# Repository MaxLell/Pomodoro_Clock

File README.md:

# Pomodoro_Clock

## Why?
This device forces me to take breaks in regular intervals throughout the day. Research has shown that the brain grows tired when being forced to focus on tasks on a prolonged time. (I think everybody can also observe this in his own life). But research also shows, that if you take regular breaks, you do not deplete your mental ressources as quickly and you can focus for longer hours.

So this is basically what this device (will) is about. It will sit on my desk and ping me, when I need to take a break, and not only ping me, but rather shine a bright light at me, so that I actually get my lazy a** up and move around for a couple of minutes - day in day out. 
You might say: Well you can also set a timer on your smartphone and go from there, to which I reply: Yeah you can, but if you want to do that day-in, day-out, you need a lot of will power and the most perfect habits the world has ever witnessed in man-kind. I am not such a person. 

And for this reason I built this device.

## What?
So what is this marvelous device I am talking about? Well I am glad you are asking: It is basically a box of lights, where you can set up the interval for which you want to work (the next cycle is composed of Worktime and Breaktime). Then it will run a countdown timer.

## How?
- This project is partially also a way for myself to learn and work on a complicated challenge: I already resolved the architecture of this multi-module Architecture (using a Message Broker, so that these modules only exchange data via this Messages-Interface - Observer Pattern). Or working on the implementation of high-speed low level peripherals, which require the usage of the DMA.

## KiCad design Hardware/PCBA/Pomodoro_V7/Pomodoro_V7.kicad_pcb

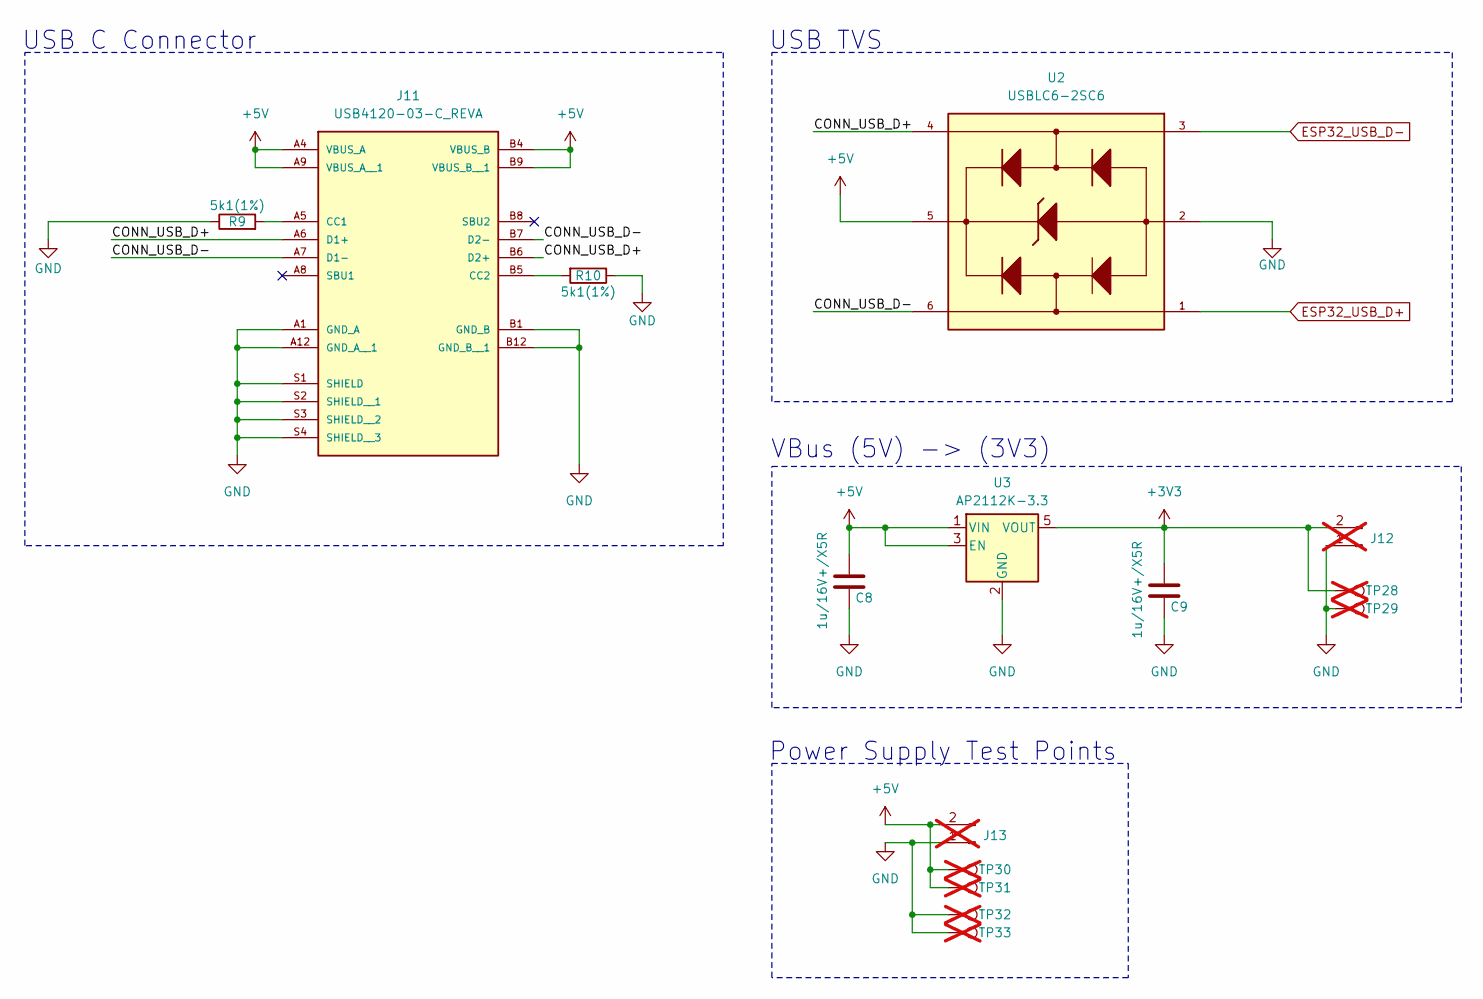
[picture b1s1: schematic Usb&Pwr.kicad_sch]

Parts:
C8, C9: 1u/16V+/X5R; C_0805_2012Metric
J11: USB4120-03-C_REVA; GCT_USB4120-03-C_REVA; PARTREV A
J12, J13: Conn_01x02_Pin; PinHeader_1x02_P2.54mm_Vertical; not fitted
R9, R10: 5k1(1%); R_0805_2012Metric; Part ID CR0805-FX-5101ELF
TP28, TP29, TP30, TP31, TP32, TP33: TestPoint; TestPoint_Pad_D1.0mm; not fitted
U2: USBLC6-2SC6; SOT95P280X145-6N; Mfg Part # USBLC6-2SC6
U3: AP2112K-3.3; SOT-23-5; Mfg Part # AP2112K-3.3TRG1

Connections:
+3V3: C9.1, J12.2, TP28.1, U3.5 (VOUT); also elsewhere on the board
+5V: C8.1, J11.A4 (VBUS_A), J11.A9 (VBUS_A__1), J11.B4 (VBUS_B), J11.B9 (VBUS_B__1), J13.2, TP30.1, TP31.1, U2.5, U3.1 (VIN), U3.3 (EN); also elsewhere on the board
/USB Conn and PWR /CONN_USB_D+: J11.A6 (D1+), J11.B6 (D2+), U2.4
/USB Conn and PWR /CONN_USB_D-: J11.A7 (D1-), J11.B7 (D2-), U2.6
ESP32_USB_D+: U2.1; also elsewhere on the board
ESP32_USB_D-: U2.3; also elsewhere on the board
GND: C8.2, C9.2, J11.A1 (GND_A), J11.A12 (GND_A__1), J11.B1 (GND_B), J11.B12 (GND_B__1), J11.S1 (SHIELD), J11.S2 (SHIELD__1), J11.S3 (SHIELD__2), J11.S4 (SHIELD__3), J12.1, J13.1, R9.1, R10.1, TP29.1, TP32.1, TP33.1, U2.2, U3.2 (GND); also elsewhere on the board
unnamed: J11.A5 (CC1), R9.2
unnamed: J11.B5 (CC2), R10.2

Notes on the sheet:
USB TVS
Power Supply Test Points
VBus (5V) -> (3V3)
USB C Connector

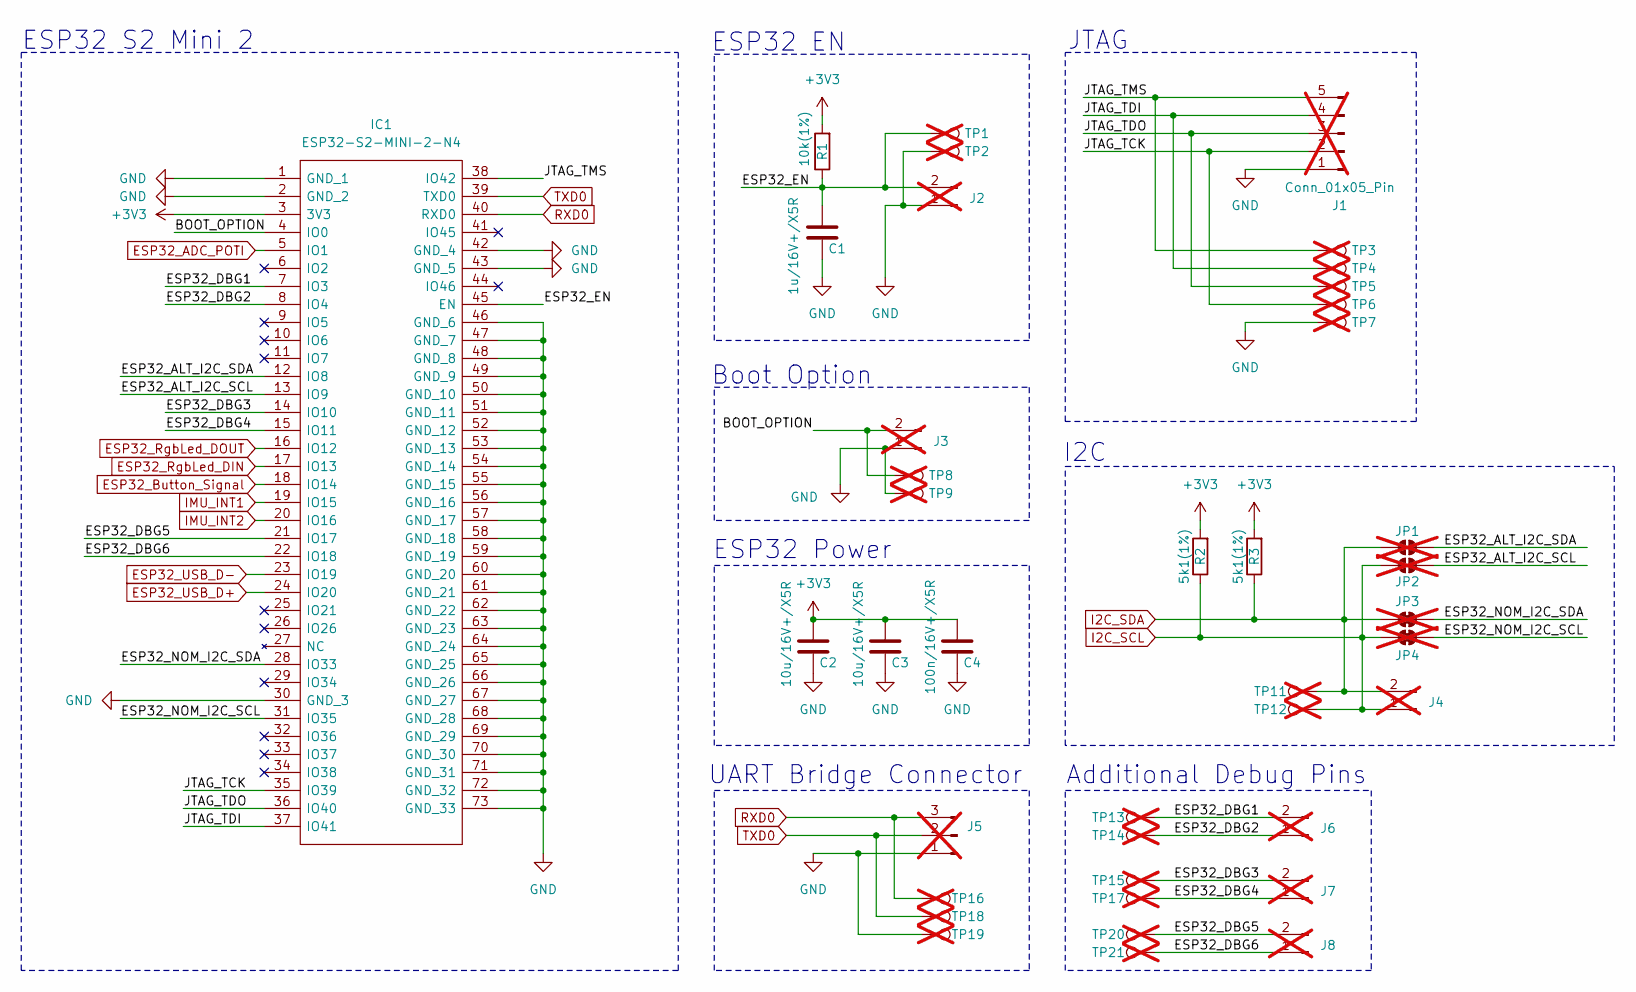
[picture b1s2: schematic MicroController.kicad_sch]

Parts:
C1: 1u/16V+/X5R; C_0805_2012Metric
C2, C3: 10u/16V+/X5R; C_0805_2012Metric
C4: 100n/16V+/X5R; C_0805_2012Metric
IC1: ESP32-S2-MINI-2-N4; ESP32-S2-MINI-1; Mouser Part Number 356-ESP32MINI-2-N4
J1: Conn_01x05_Pin; PinHeader_1x05_P2.54mm_Vertical; not fitted
J2, J3, J4, J6, J7, J8: Conn_01x02_Pin; PinHeader_1x02_P2.54mm_Vertical; not fitted
J5: Conn_01x03_Pin; PinHeader_1x03_P2.54mm_Vertical; not fitted
JP1, JP2: SolderJumper_2_Open; SolderJumper-2_P1.3mm_Open_RoundedPad1.0x1.5mm; not fitted
JP3, JP4: SolderJumper_2_Bridged; SolderJumper-2_P1.3mm_Bridged2Bar_RoundedPad1.0x1.5mm; not fitted
R1: 10k(1%); R_0805_2012Metric; Part ID CR0805-FX-5101ELF
R2, R3: 5k1(1%); R_0805_2012Metric; Part ID CR0805-FX-5101ELF
TP1, TP2, TP3, TP4, TP5, TP6, TP7, TP8, TP9, TP11, TP12, TP13, TP14, TP15, TP16, TP17, TP18, TP19, TP20, TP21: TestPoint; TestPoint_Pad_D1.0mm; not fitted

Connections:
+3V3: C2.1, C3.1, C4.1, IC1.3 (3V3), R1.2, R2.2, R3.2; also elsewhere on the board
/MicroController/BOOT_OPTION: IC1.4 (IO0), J3.2, TP8.1
/MicroController/ESP32_ALT_I2C_SCL: IC1.13 (IO9), JP2.1 (A)
/MicroController/ESP32_ALT_I2C_SDA: IC1.12 (IO8), JP1.2 (B)
/MicroController/ESP32_DBG1: IC1.7 (IO3), J6.2, TP13.1
/MicroController/ESP32_DBG2: IC1.8 (IO4), J6.1, TP14.1
/MicroController/ESP32_DBG3: IC1.14 (IO10), J7.2, TP15.1
/MicroController/ESP32_DBG4: IC1.15 (IO11), J7.1, TP17.1
/MicroController/ESP32_DBG5: IC1.21 (IO17), J8.2, TP20.1
/MicroController/ESP32_DBG6: IC1.22 (IO18), J8.1, TP21.1
/MicroController/ESP32_EN: C1.1, IC1.45 (EN), J2.2, R1.1, TP1.1
/MicroController/ESP32_NOM_I2C_SCL: IC1.31 (IO35), JP4.1 (A)
/MicroController/ESP32_NOM_I2C_SDA: IC1.28 (IO33), JP3.2 (B)
/MicroController/JTAG_TCK: IC1.35 (IO39), J1.2, TP6.1
/MicroController/JTAG_TDI: IC1.37 (IO41), J1.4, TP4.1
/MicroController/JTAG_TDO: IC1.36 (IO40), J1.3, TP5.1
/MicroController/JTAG_TMS: IC1.38 (IO42), J1.5, TP3.1
ESP32_ADC_POTI: IC1.5 (IO1); also elsewhere on the board
ESP32_Button_Signal: IC1.18 (IO14); also elsewhere on the board
ESP32_RgbLed_DIN: IC1.17 (IO13); also elsewhere on the board
ESP32_RgbLed_DOUT: IC1.16 (IO12); also elsewhere on the board
ESP32_USB_D+: IC1.24 (IO20); also elsewhere on the board
ESP32_USB_D-: IC1.23 (IO19); also elsewhere on the board
GND: C1.2, C2.2, C3.2, C4.2, IC1.1 (GND_1), IC1.2 (GND_2), IC1.30 (GND_3), IC1.42 (GND_4), IC1.43 (GND_5), IC1.46 (GND_6), IC1.47 (GND_7), IC1.48 (GND_8), IC1.49 (GND_9), IC1.50 (GND_10), IC1.51 (GND_11), IC1.52 (GND_12), IC1.53 (GND_13), IC1.54 (GND_14), IC1.55 (GND_15), IC1.56 (GND_16), IC1.57 (GND_17), IC1.58 (GND_18), IC1.59 (GND_19), IC1.60 (GND_20), IC1.61 (GND_21), IC1.62 (GND_22), IC1.63 (GND_23), IC1.64 (GND_24), IC1.65 (GND_25), IC1.66 (GND_26), IC1.67 (GND_27), IC1.68 (GND_28), IC1.69 (GND_29), IC1.70 (GND_30), IC1.71 (GND_31), IC1.72 (GND_32), IC1.73 (GND_33), J1.1, J2.1, J3.1, J5.1, TP2.1, TP7.1, TP9.1, TP19.1; also elsewhere on the board
I2C_SCL: J4.1, JP2.2 (B), JP4.2 (B), R2.1, TP12.1; also elsewhere on the board
I2C_SDA: J4.2, JP1.1 (A), JP3.1 (A), R3.1, TP11.1; also elsewhere on the board
IMU_INT1: IC1.19 (IO15); also elsewhere on the board
IMU_INT2: IC1.20 (IO16); also elsewhere on the board
RXD0: IC1.40 (RXD0), J5.3, TP16.1
TXD0: IC1.39 (TXD0), J5.2, TP18.1

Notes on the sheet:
ESP32 Power
ESP32 EN
Additional Debug Pins
ESP32 S2 Mini 2
UART Bridge Connector
JTAG
I2C
Boot Option

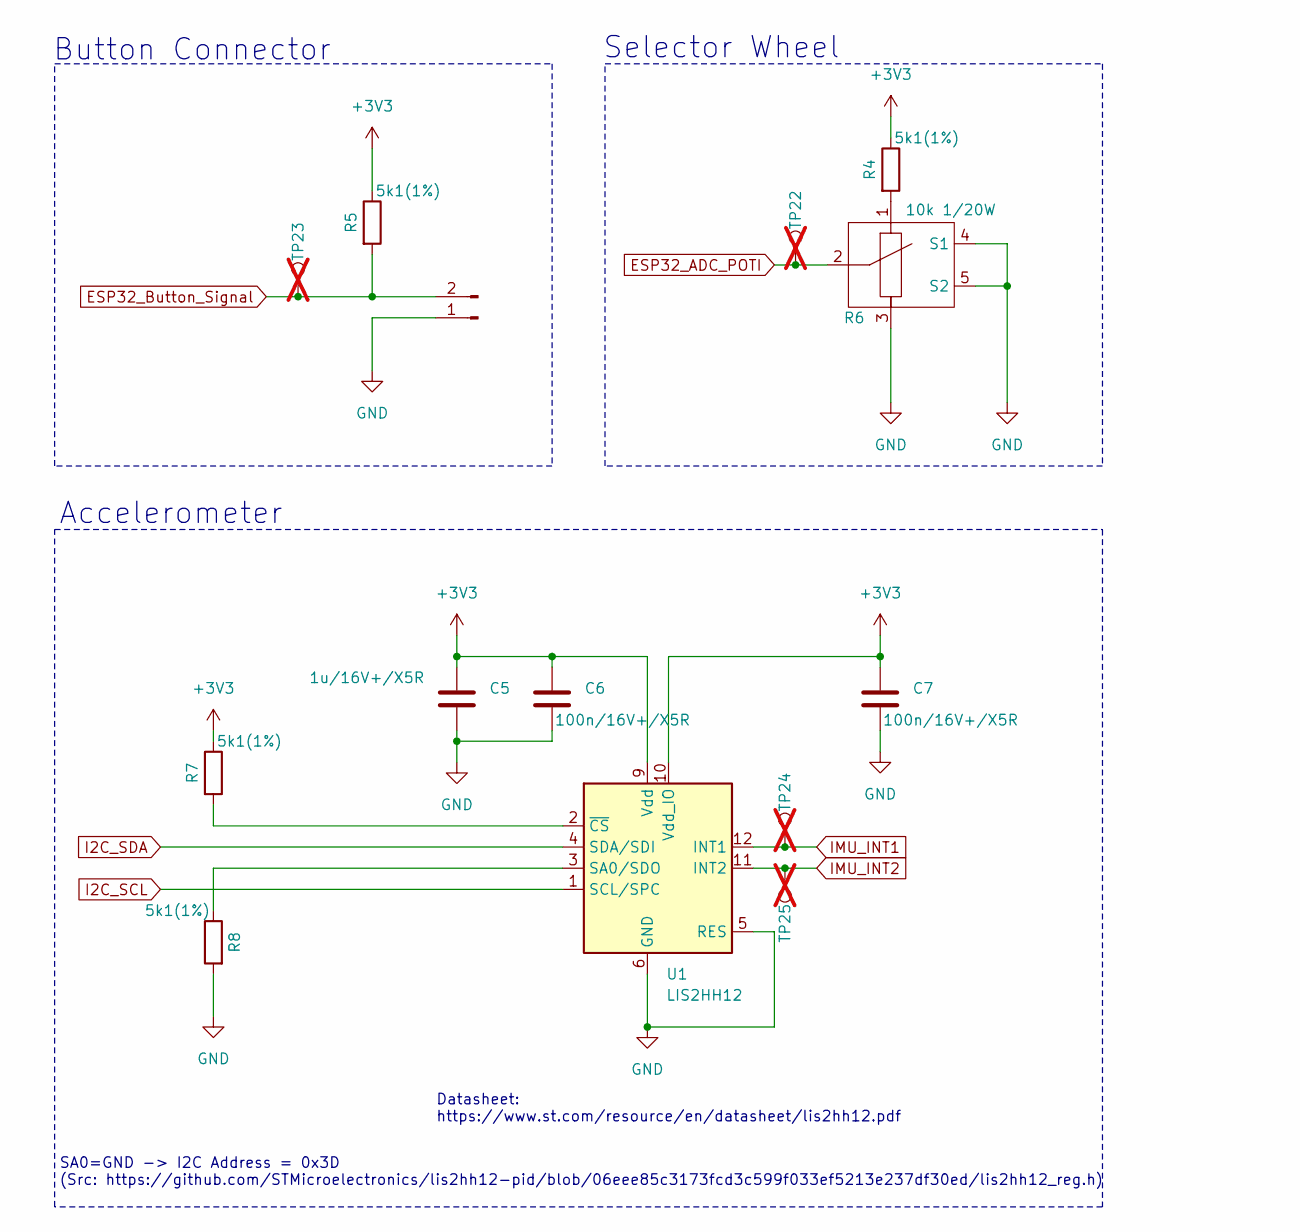
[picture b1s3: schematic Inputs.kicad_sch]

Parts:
C5: 1u/16V+/X5R; C_0805_2012Metric; MPN 0805B105K250DC
C6, C7: 100n/16V+/X5R; C_0805_2012Metric; MPN CC0805KRX7R9BB104
J10: Conn_01x02_Pin; PinHeader_1x02_P2.54mm_Horizontal
R4, R5, R7, R8: 5k1(1%); R_0805_2012Metric; Part ID CR0805-FX-5101ELF
R6: 10k 1/20W; Pot; Mfg Part # PTV09A-4025F-B103
TP22, TP23, TP24, TP25: TestPoint; TestPoint_Pad_D1.0mm; not fitted
U1: LIS2HH12; Kionix_LGA-12_2x2mm_P0.5mm_LayoutBorder2x4y; MPN LIS2HH12

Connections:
+3V3: C5.2, C6.2, C7.2, R4.1, R5.1, R7.1, U1.9 (Vdd), U1.10 (Vdd_IO); also elsewhere on the board
ESP32_ADC_POTI: R6.2, TP22.1; also elsewhere on the board
ESP32_Button_Signal: J10.2, R5.2, TP23.1; also elsewhere on the board
GND: C5.1, C6.1, C7.1, J10.1, R6.3, R6.4 (S1), R6.5 (S2), R8.2, U1.5 (RES), U1.6 (GND), U1.7 (GND), U1.8 (GND); also elsewhere on the board
I2C_SCL: U1.1 (SCL/SPC); also elsewhere on the board
I2C_SDA: U1.4 (SDA/SDI); also elsewhere on the board
IMU_INT1: TP24.1, U1.12 (INT1); also elsewhere on the board
IMU_INT2: TP25.1, U1.11 (INT2); also elsewhere on the board
unnamed: R4.2, R6.1
unnamed: R8.1, U1.3 (SA0/SDO)
unnamed: R7.2, U1.2 (~CS)

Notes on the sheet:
Accelerometer
SA0=GND -> I2C Address = 0x3D (Src: https://github.com/STMicroelectronics/lis2hh12-pid/blob/06eee85c3173fcd3c599f033ef5213e237df30ed/lis2hh12_reg.h)
Button Connector
Datasheet: https://www.st.com/resource/en/datasheet/lis2hh12.pdf
Selector Wheel

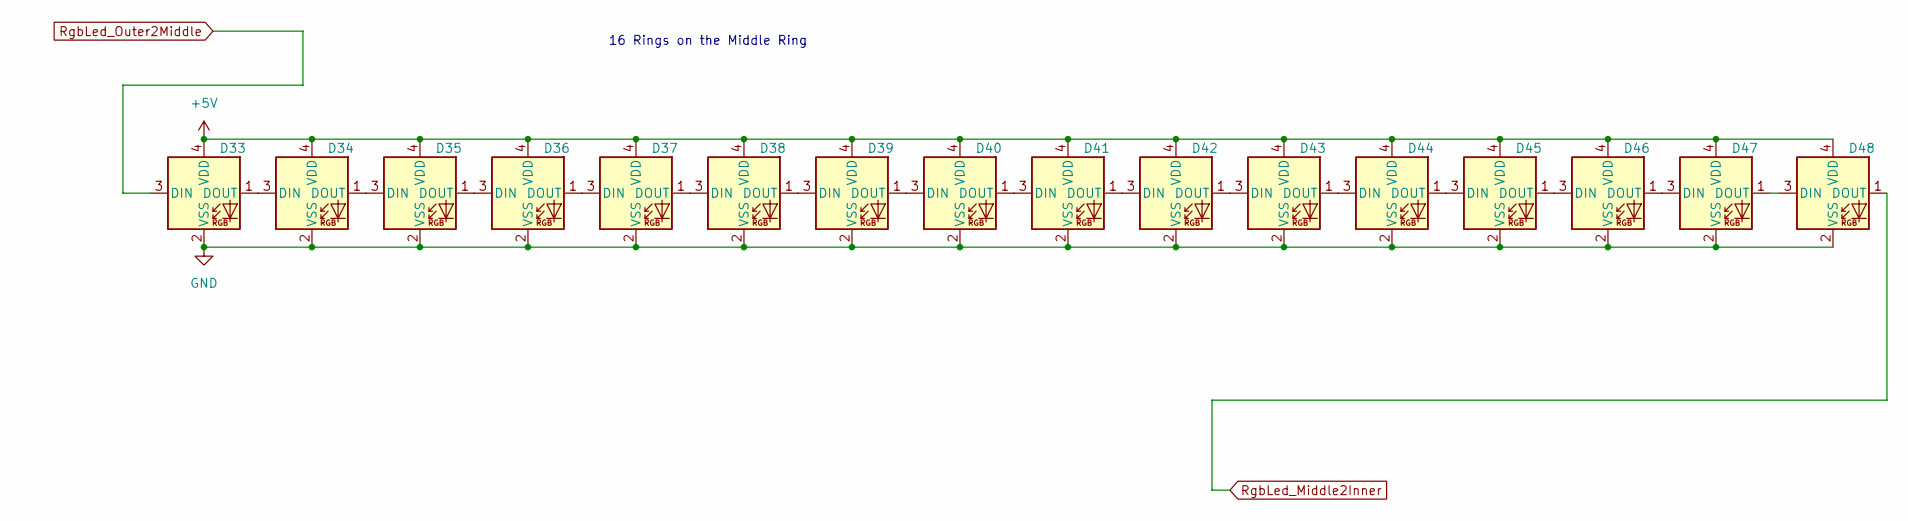
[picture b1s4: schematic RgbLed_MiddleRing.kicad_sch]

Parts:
D33, D34, D35, D36, D37, D38, D39, D40, D41, D42, D43, D44, D45, D46, D47, D48: WS2812B-2020; LED_WS2812B-2020_PLCC4_2.0x2.0mm; MPN WS2812B-2020

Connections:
+5V: D33.4 (VDD), D34.4 (VDD), D35.4 (VDD), D36.4 (VDD), D37.4 (VDD), D38.4 (VDD), D39.4 (VDD), D40.4 (VDD), D41.4 (VDD), D42.4 (VDD), D43.4 (VDD), D44.4 (VDD), D45.4 (VDD), D46.4 (VDD), D47.4 (VDD), D48.4 (VDD); also elsewhere on the board
GND: D33.2 (VSS), D34.2 (VSS), D35.2 (VSS), D36.2 (VSS), D37.2 (VSS), D38.2 (VSS), D39.2 (VSS), D40.2 (VSS), D41.2 (VSS), D42.2 (VSS), D43.2 (VSS), D44.2 (VSS), D45.2 (VSS), D46.2 (VSS), D47.2 (VSS), D48.2 (VSS); also elsewhere on the board
unnamed: D33.1 (DOUT), D34.3 (DIN)
unnamed: D34.1 (DOUT), D35.3 (DIN)
unnamed: D35.1 (DOUT), D36.3 (DIN)
unnamed: D36.1 (DOUT), D37.3 (DIN)
unnamed: D37.1 (DOUT), D38.3 (DIN)
unnamed: D38.1 (DOUT), D39.3 (DIN)
unnamed: D39.1 (DOUT), D40.3 (DIN)
unnamed: D40.1 (DOUT), D41.3 (DIN)
unnamed: D41.1 (DOUT), D42.3 (DIN)
unnamed: D42.1 (DOUT), D43.3 (DIN)
unnamed: D43.1 (DOUT), D44.3 (DIN)
unnamed: D44.1 (DOUT), D45.3 (DIN)
unnamed: D45.1 (DOUT), D46.3 (DIN)
unnamed: D46.1 (DOUT), D47.3 (DIN)
unnamed: D47.1 (DOUT), D48.3 (DIN)
RgbLed_Middle2Inner: D48.1 (DOUT); also elsewhere on the board
RgbLed_Outer2Middle: D33.3 (DIN); also elsewhere on the board

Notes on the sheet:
16 Rings on the Middle Ring

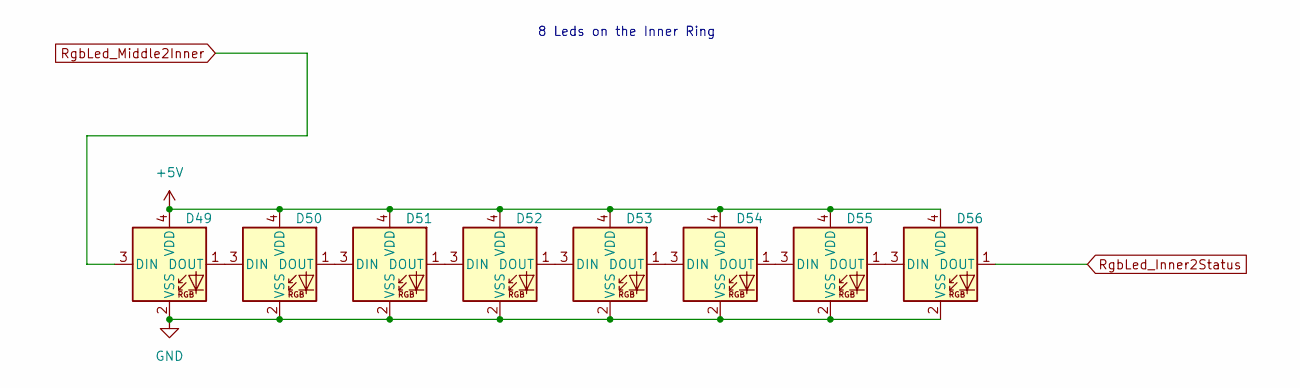
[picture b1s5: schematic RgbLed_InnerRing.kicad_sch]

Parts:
D49, D50, D51, D52, D53, D54, D55, D56: WS2812B-2020; LED_WS2812B-2020_PLCC4_2.0x2.0mm; MPN WS2812B-2020

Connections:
+5V: D49.4 (VDD), D50.4 (VDD), D51.4 (VDD), D52.4 (VDD), D53.4 (VDD), D54.4 (VDD), D55.4 (VDD), D56.4 (VDD); also elsewhere on the board
GND: D49.2 (VSS), D50.2 (VSS), D51.2 (VSS), D52.2 (VSS), D53.2 (VSS), D54.2 (VSS), D55.2 (VSS), D56.2 (VSS); also elsewhere on the board
unnamed: D49.1 (DOUT), D50.3 (DIN)
unnamed: D50.1 (DOUT), D51.3 (DIN)
unnamed: D51.1 (DOUT), D52.3 (DIN)
unnamed: D52.1 (DOUT), D53.3 (DIN)
unnamed: D53.1 (DOUT), D54.3 (DIN)
unnamed: D54.1 (DOUT), D55.3 (DIN)
unnamed: D55.1 (DOUT), D56.3 (DIN)
RgbLed_Inner2Status: D56.1 (DOUT); also elsewhere on the board
RgbLed_Middle2Inner: D49.3 (DIN); also elsewhere on the board

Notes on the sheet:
8 Leds on the Inner Ring

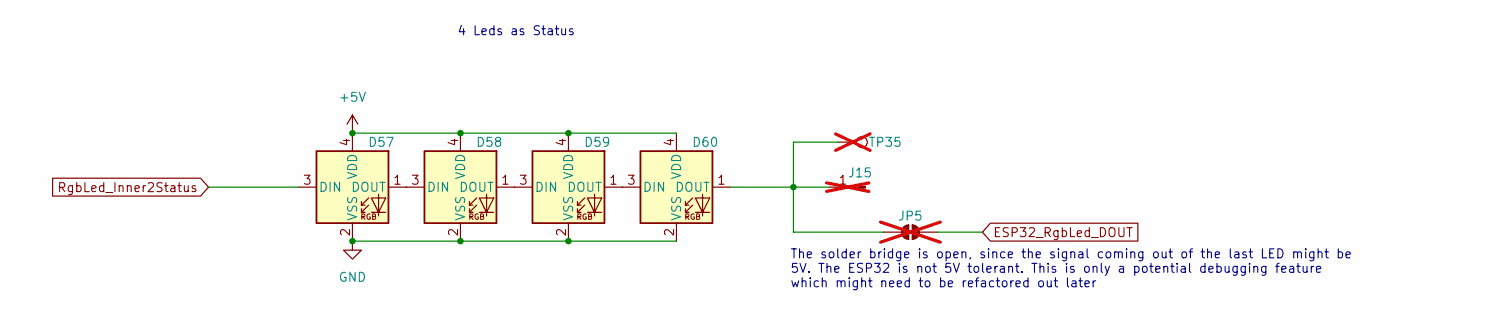
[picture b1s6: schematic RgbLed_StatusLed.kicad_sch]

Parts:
D57, D58, D59, D60: WS2812B-2020; LED_WS2812B-2020_PLCC4_2.0x2.0mm; MPN WS2812B-2020
J15: Conn_01x01_Pin; PinHeader_1x01_P2.54mm_Vertical; not fitted
JP5: SolderJumper_2_Open; SolderJumper-2_P1.3mm_Open_RoundedPad1.0x1.5mm; not fitted
TP35: TestPoint; TestPoint_Pad_D1.0mm; not fitted

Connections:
+5V: D57.4 (VDD), D58.4 (VDD), D59.4 (VDD), D60.4 (VDD); also elsewhere on the board
ESP32_RgbLed_DOUT: JP5.2 (B); also elsewhere on the board
GND: D57.2 (VSS), D58.2 (VSS), D59.2 (VSS), D60.2 (VSS); also elsewhere on the board
unnamed: D57.1 (DOUT), D58.3 (DIN)
unnamed: D58.1 (DOUT), D59.3 (DIN)
unnamed: D59.1 (DOUT), D60.3 (DIN)
unnamed: D60.1 (DOUT), J15.1, JP5.1 (A), TP35.1
RgbLed_Inner2Status: D57.3 (DIN); also elsewhere on the board

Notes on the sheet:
4 Leds as Status
The solder bridge is open, since the signal coming out of the last LED might be 5V. The ESP32 is not 5V tolerant. This is only a potential debugging feature which might need to be refactored out later

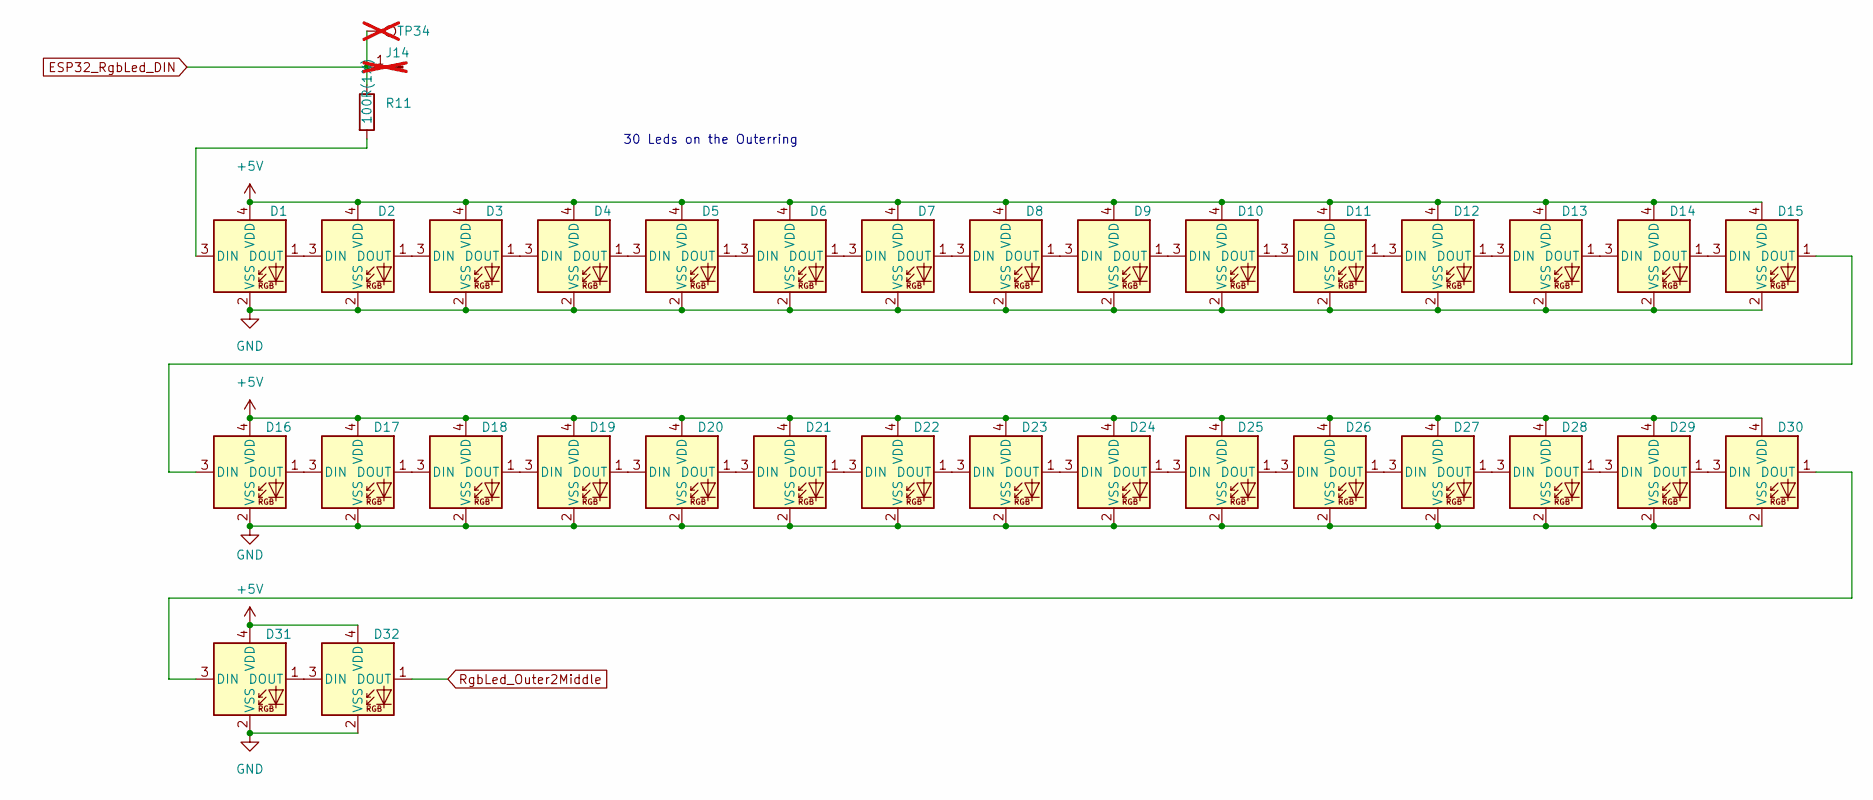
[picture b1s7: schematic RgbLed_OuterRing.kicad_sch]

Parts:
D1, D2, D3, D4, D5, D6, D7, D8, D9, D10, D11, D12, D13, D14, D15, D16, D17, D18, D19, D20, D21, D22, D23, D24, D25, D26, D27, D28, D29, D30, D31, D32: WS2812B-2020; LED_WS2812B-2020_PLCC4_2.0x2.0mm; MPN WS2812B-2020
J14: Conn_01x01_Pin; PinHeader_1x01_P2.54mm_Vertical; not fitted
R11: 100R(1%); R_0805_2012Metric; MPN RC0805FR-07100RL
TP34: TestPoint; TestPoint_Pad_D1.0mm; not fitted

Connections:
+5V: D1.4 (VDD), D2.4 (VDD), D3.4 (VDD), D4.4 (VDD), D5.4 (VDD), D6.4 (VDD), D7.4 (VDD), D8.4 (VDD), D9.4 (VDD), D10.4 (VDD), D11.4 (VDD), D12.4 (VDD), D13.4 (VDD), D14.4 (VDD), D15.4 (VDD), D16.4 (VDD), D17.4 (VDD), D18.4 (VDD), D19.4 (VDD), D20.4 (VDD), D21.4 (VDD), D22.4 (VDD), D23.4 (VDD), D24.4 (VDD), D25.4 (VDD), D26.4 (VDD), D27.4 (VDD), D28.4 (VDD), D29.4 (VDD), D30.4 (VDD), D31.4 (VDD), D32.4 (VDD); also elsewhere on the board
ESP32_RgbLed_DIN: J14.1, R11.1, TP34.1; also elsewhere on the board
GND: D1.2 (VSS), D2.2 (VSS), D3.2 (VSS), D4.2 (VSS), D5.2 (VSS), D6.2 (VSS), D7.2 (VSS), D8.2 (VSS), D9.2 (VSS), D10.2 (VSS), D11.2 (VSS), D12.2 (VSS), D13.2 (VSS), D14.2 (VSS), D15.2 (VSS), D16.2 (VSS), D17.2 (VSS), D18.2 (VSS), D19.2 (VSS), D20.2 (VSS), D21.2 (VSS), D22.2 (VSS), D23.2 (VSS), D24.2 (VSS), D25.2 (VSS), D26.2 (VSS), D27.2 (VSS), D28.2 (VSS), D29.2 (VSS), D30.2 (VSS), D31.2 (VSS), D32.2 (VSS); also elsewhere on the board
unnamed: D1.3 (DIN), R11.2
unnamed: D1.1 (DOUT), D2.3 (DIN)
unnamed: D2.1 (DOUT), D3.3 (DIN)
unnamed: D3.1 (DOUT), D4.3 (DIN)
unnamed: D4.1 (DOUT), D5.3 (DIN)
unnamed: D5.1 (DOUT), D6.3 (DIN)
unnamed: D6.1 (DOUT), D7.3 (DIN)
unnamed: D7.1 (DOUT), D8.3 (DIN)
unnamed: D8.1 (DOUT), D9.3 (DIN)
unnamed: D9.1 (DOUT), D10.3 (DIN)
unnamed: D10.1 (DOUT), D11.3 (DIN)
unnamed: D11.1 (DOUT), D12.3 (DIN)
unnamed: D12.1 (DOUT), D13.3 (DIN)
unnamed: D13.1 (DOUT), D14.3 (DIN)
unnamed: D14.1 (DOUT), D15.3 (DIN)
unnamed: D15.1 (DOUT), D16.3 (DIN)
unnamed: D16.1 (DOUT), D17.3 (DIN)
unnamed: D17.1 (DOUT), D18.3 (DIN)
unnamed: D18.1 (DOUT), D19.3 (DIN)
unnamed: D19.1 (DOUT), D20.3 (DIN)
unnamed: D20.1 (DOUT), D21.3 (DIN)
unnamed: D21.1 (DOUT), D22.3 (DIN)
unnamed: D22.1 (DOUT), D23.3 (DIN)
unnamed: D23.1 (DOUT), D24.3 (DIN)
unnamed: D24.1 (DOUT), D25.3 (DIN)
unnamed: D25.1 (DOUT), D26.3 (DIN)
unnamed: D26.1 (DOUT), D27.3 (DIN)
unnamed: D27.1 (DOUT), D28.3 (DIN)
unnamed: D28.1 (DOUT), D29.3 (DIN)
unnamed: D29.1 (DOUT), D30.3 (DIN)
unnamed: D30.1 (DOUT), D31.3 (DIN)
unnamed: D31.1 (DOUT), D32.3 (DIN)
RgbLed_Outer2Middle: D32.1 (DOUT); also elsewhere on the board

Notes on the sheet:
30 Leds on the Outerring

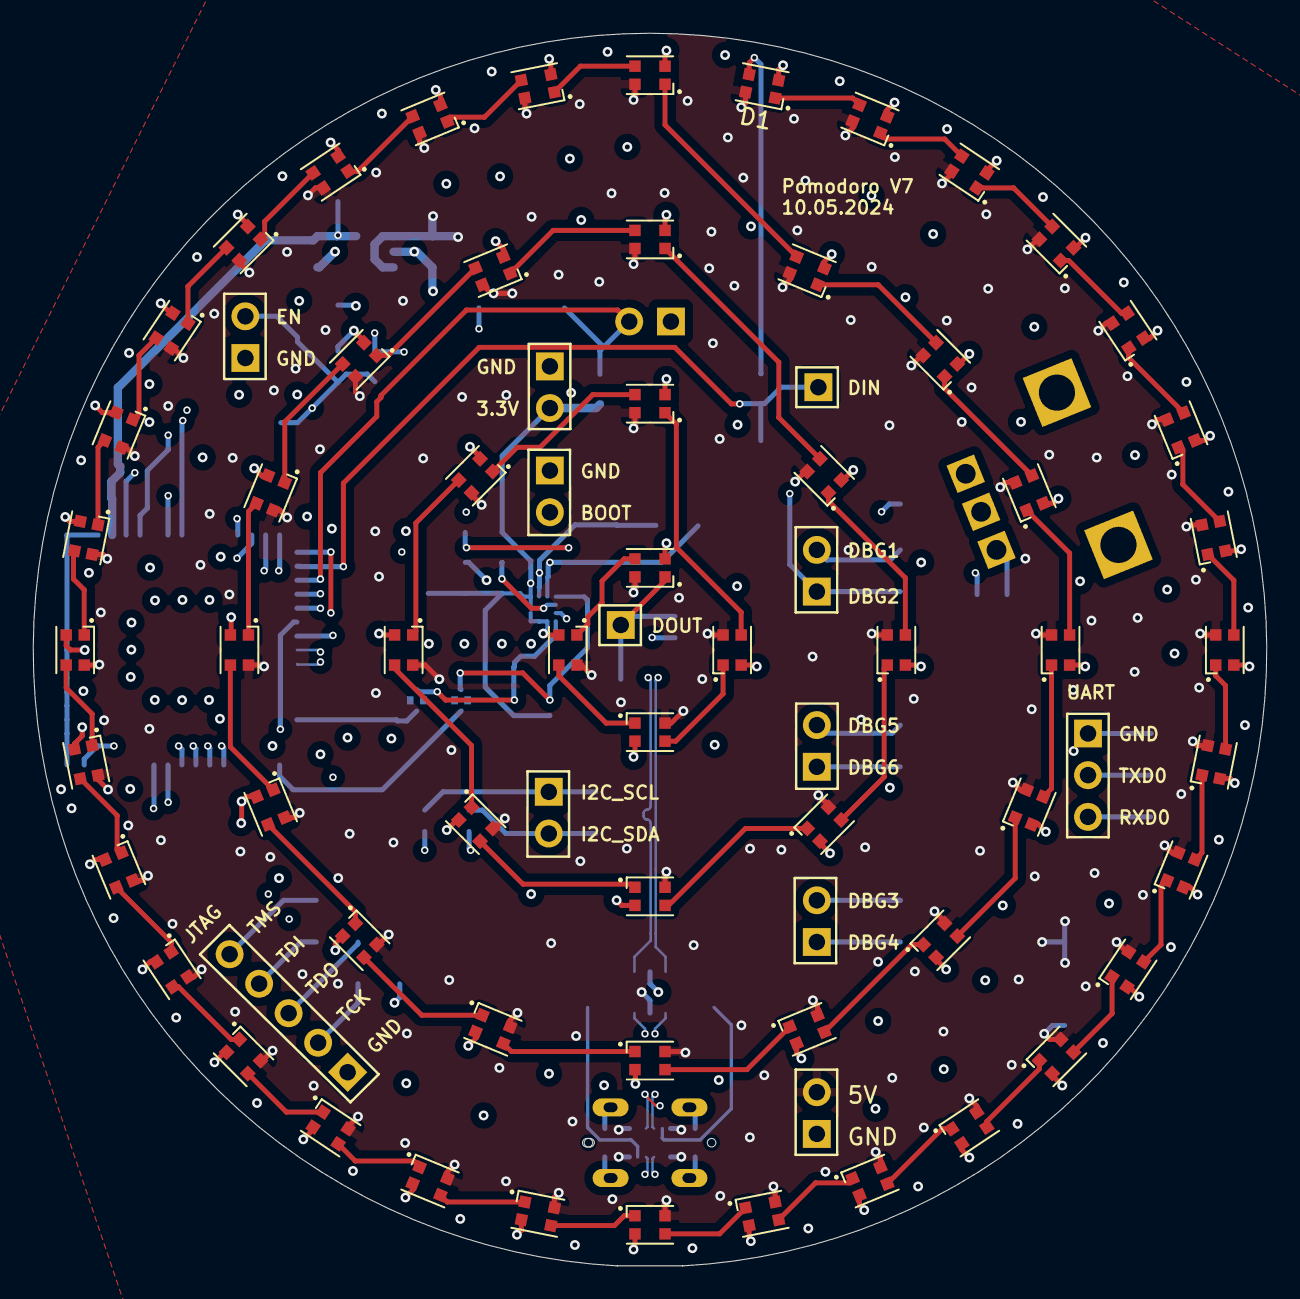
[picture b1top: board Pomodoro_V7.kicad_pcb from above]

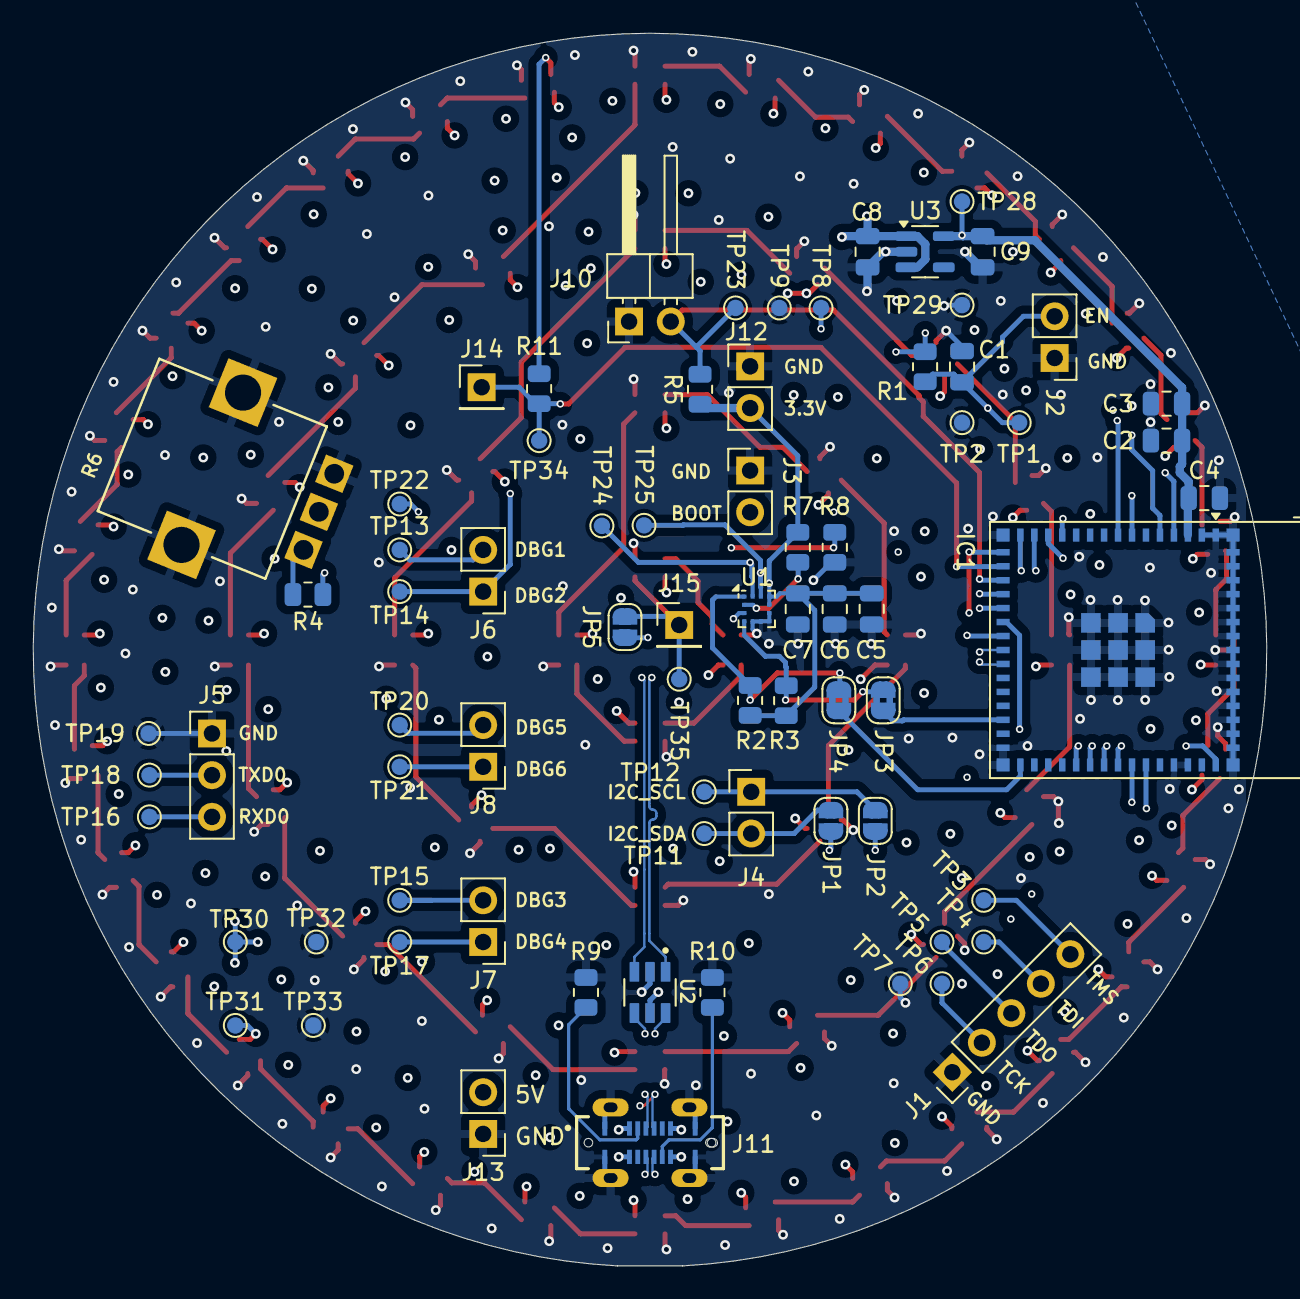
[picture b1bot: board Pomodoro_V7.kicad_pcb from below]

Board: 4 copper layers, 75.1 x 75.1 mm, 135 parts (75 on the bottom side), 99 nets.

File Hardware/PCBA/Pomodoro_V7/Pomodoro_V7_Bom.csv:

"Reference","Qty","Value","Mfg Part #","Datasheet","Footprint","DNP"
"C1,C5,C8,C9","4","1u/16V+/X5R","","~","Capacitor_SMD:C_0805_2012Metric",""
"C2,C3","2","10u/16V+/X5R","","~","Capacitor_SMD:C_0805_2012Metric",""
"C4,C6,C7","3","100n/16V+/X5R","","~","Capacitor_SMD:C_0805_2012Metric",""
"J11","1","USB4120-03-C_REVA","USB4120-03-C","https://mm.digikey.com/Volume0/opasdata/d220001/medias/docus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","Connector:GCT_USB4120-03-C_REVA",""
"J10","1","Conn_01x02_Pin","","~","Connector_PinHeader_2.54mm:PinHeader_1x02_P2.54mm_Horizontal",""
"U2","1","USBLC6-2SC6","USBLC6-2SC6","","Diode_SMD:SOT95P280X145-6N",""
"D1,D2,D3,D4,D5,D6,D7,D8,D9,D10,D11,D12,D13,D14,D15,D16,D17,D18,D19,D20,D21,D22,D23,D24,D25,D26,D27,D28,D29,D30,D31,D32,D33,D34,D35,D36,D37,D38,D39,D40,D41,D42,D43,D44,D45,D46,D47,D48,D49,D50,D51,D52,D53,D54,D55,D56,D57,D58,D59,D60","60","WS2812B-2020","","https://cdn-shop.adafruit.com/product-files/4684/4684_WS2812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","LED_SMD:LED_WS2812B-2020_PLCC4_2.0x2.0mm",""
"U1","1","LIS2HH12","LIS2HH12TR","www.st.com/resource/en/datasheet/lis2hh12.pdf","Package_LGA:Kionix_LGA-12_2x2mm_P0.5mm_LayoutBorder2x4y",""
"U3","1","AP2112K-3.3","AP2112K-3.3TRG1","https://www.diodes.com/assets/Datasheets/AP2112.pdf","Package_TO_SOT_SMD:SOT-23-5",""
"R6","1","10k 1/20W","PTV09A-4025F-B103","https://eu.mouser.com/datasheet/2/54/ptv09-777818.pdf","Potentiometer_THT:Pot",""
"R1","1","10k(1%)","","~","Resistor_SMD:R_0805_2012Metric",""
"R2,R3,R4,R5,R7,R8,R9,R10","8","5k1(1%)","","~","Resistor_SMD:R_0805_2012Metric",""
"R11","1","100R(1%)","","~","Resistor_SMD:R_0805_2012Metric",""
"IC1","1","ESP32-S2-MINI-2-N4","ESP32-S2-MINI-2-N4","https://www.espressif.com/sites/default/files/documentation/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","RF_Module:ESP32-S2-MINI-1",""
